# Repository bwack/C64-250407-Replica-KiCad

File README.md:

# The C64 250407 replica

A replica of the Commodore 64 Ver.250407  Rev.B motherboard, and matching schematics.

The replica project was started by Michael K. (Der Alte Bastler) in 2019 to learn SprintLayout, and the process of reverse engineering printed circuit boards. I finished the layout in SprintLayout, and imported it to KiCad. The KU motherboard schematics are nowhere to be found on the internet. Therefore I used the 250407 Reb.B schematics as reference and then modified them to match the KU motherboard layout.

The board has been prototyped and tested by Langwell Cowan and I.

We are not the first to reverse engineer this board; but we are the first to share the design files online.

# BOM

Please see the [BOM file](250407_bom.csv).

Note that some values were left blank because they depend on the clock circuit (PAL/NTSC), and PLA model. They never made it into the schematics. You can find them in a table to the right of the schematics for 250407.
http://www.zimmers.net/anonftp/pub/cbm/schematics/computers/c64/index.html

# Interactive-BOM

[The interactive bom html page](https://htmlpreview.github.io/?https://raw.githubusercontent.com/bwack/C64-250407-Replica-KiCad/main/interactive-bom/ibom.html) is a useful tool for assembling the board and finding signal traces via a web browser. To order parts, Use the BOM document listed above. (Mouser and Digikey compatable)

# Schematics

Download the PDF file [250407_.pdf](250407_.pdf) for high quality schematics.
Checkout [this tweet](https://twitter.com/paulrickards/status/1371988589974847492) by Paul Rickards where he plots the KU motherboard schematics KU-14194HB :-)

# Change log
- 2025-06-09: PCB and Schematics V1.3: PAL-NTSC jumpers fox. Thank you, Fred Sauer!
Note: V1.3 was opened and saved in KiCAD 9.0.1. I've verified the new gerbers. Things to beware of I you want to modify the design: 1. If you try to load changes from schematic into the PCBNew, KiCAD will require you to annotate the schematics, which in turn will replace all the resistor array sub parts. Example R1A will become R1A1, which will turn into new parts in PCBNew. Therefore I have not done that in this update. I have only changed the silkscreen, and I have only edited the schematics. 2. KiCAD will ask you to refill the zone fills. I have not done that because it also warns you about some change in fill-constrains. I don't remember exactly what, but I did not refill the fill zones when going to V1.3.
- 2022-08-18: Schematics V1.2: symbol and ERC fixes (Pull request from Gabriele Gorla/GGLABS)
- 2020-06-19: PCB and schematics V1.1: First release
- 2020-04-22: PCB and schematics V1.0: Prototype

# YouTube

Part 1-4:

# License and Disclaimer

Copyright Bwack 2025

This documentation describes Open Hardware and is licensed under the CERN OHL v. 1.2.

You may redistribute and modify this documentation under the terms of theCERN OHL v.1.2. (http://ohwr.org/cernohl). This documentation is distributed WITHOUT ANY EXPRESS OR IMPLIED WARRANTY, INCLUDING OF MERCHANTABILITY, SATISFACTORY QUALITY AND FITNESS FOR APARTICULAR PURPOSE. Please see the CERN OHL v.1.2 for applicable conditions.

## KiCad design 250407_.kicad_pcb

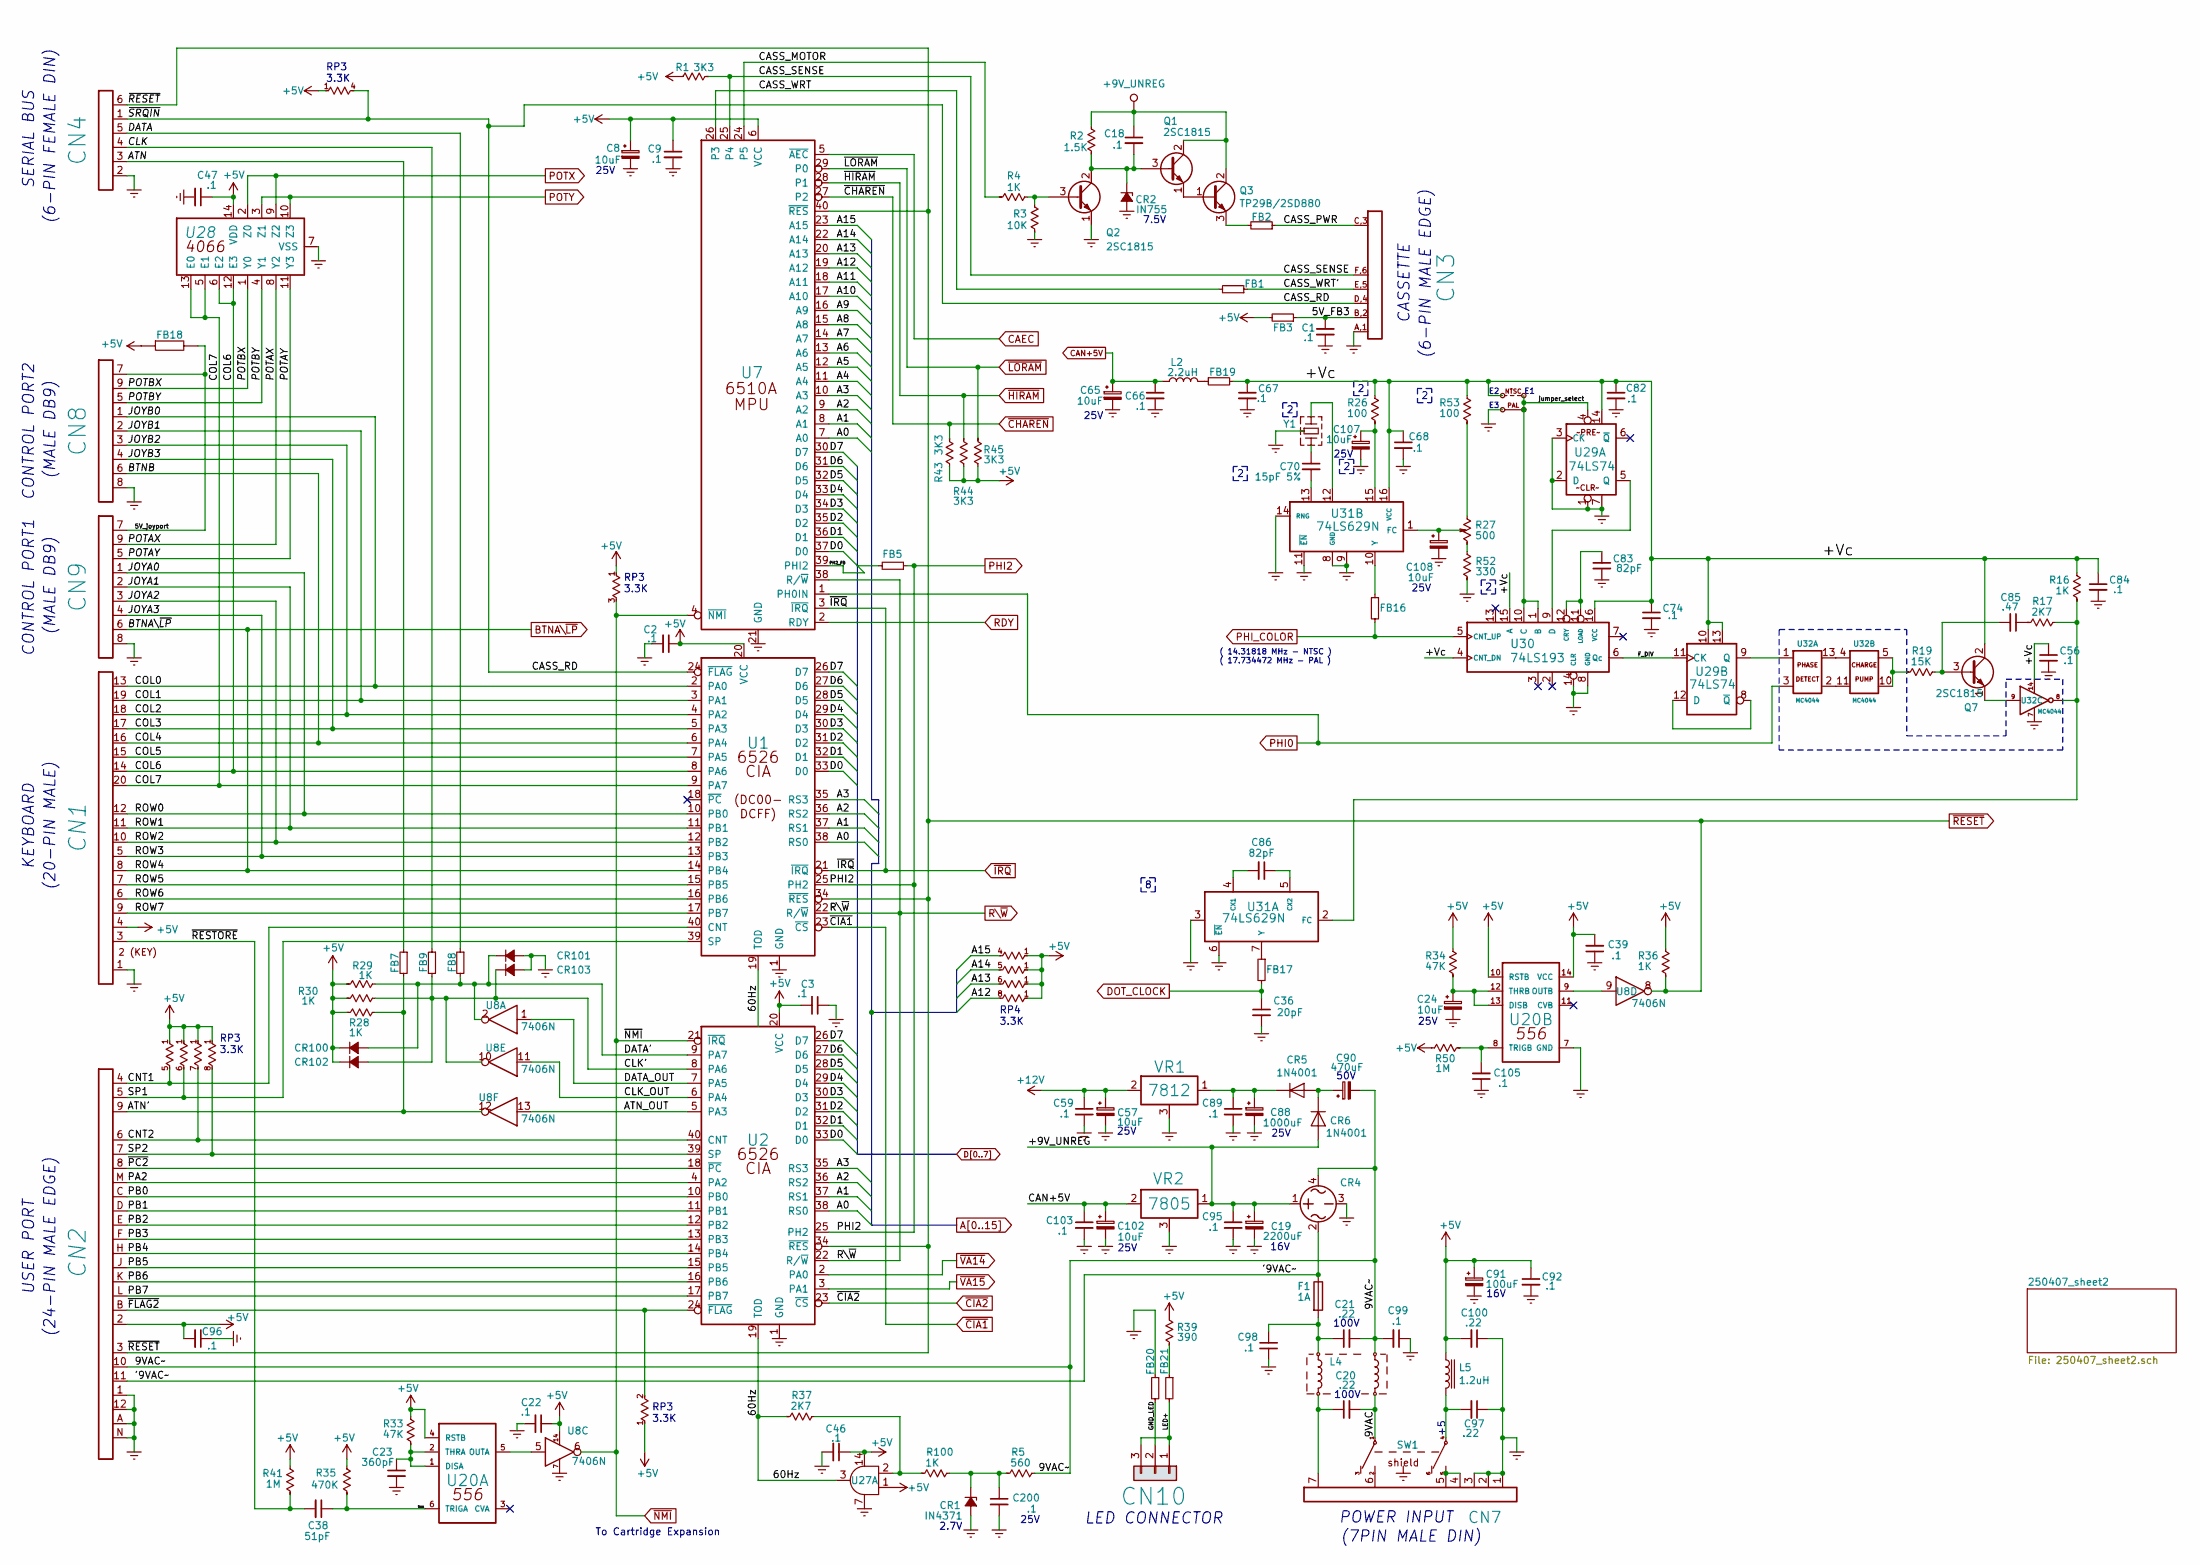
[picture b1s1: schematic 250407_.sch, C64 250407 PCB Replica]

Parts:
C1, C2, C3, C9, C18, C22, C39, C46, C47, C56, C59, C66, C67, C68, C74, C82, C84, C89, C92, C95, C96, C98, C99, C103, C105, C200: .1; CAP_P5.08mm
C8, C24, C57, C65, C102, C107, C108: 10uF; CAP_ELYT_RADIAL_P5.08mm_SMALL_RING
C19: 2200uF; LARGE_ELECTROLYTIC_AXIAL_TH
C20, C21: .22; CAP_POLY_100V_TH_P5.08_and_P12.07mm
C23: 360pF; CAP_AXIAL_P12.7mm
C36: 20pF; RESISTOR
C38: 51pF; CAP_AXIAL_P12.7mm
C70: 15pF 5%; RESISTOR
C83, C86: 82pF; RESISTOR
C85: .47; CAP_P5.08mm
C88: 1000uF; LARGE_ELECTROLYTIC_AXIAL_TH
C90: 470uF; LARGE_ELECTROLYTIC_AXIAL_TH
C91: 100uF; CAP_ELYT_RADIAL_P5.08mm
C97, C100: .22; CAP_P5.08mm
CN1: KEYBOARD_20PIN_MALE; KEYBOARD_CON
CN2: USER_PORT_CON; EDGE_CON_24P
CN3: CASSETTE_PORT_CON; EDGE_CON_12P_TAPE
CN4: SERIAL_BUS_CON; SERIAL_CON_DIN6
CN7: POWER_CON; POWER_CON_D7_250407
CN8, CN9: CONTROL_PORT; JOYPORT_DB9
CN10: LED_CONNECTOR; LED_CON
CR1: IN4371; ZENER_12.7mm
CR2: IN755; ZENER_12.7mm
CR4: BRIDGE_RECTIFIER
CR5, CR6: 1N4001; RECTIFIER_TH_P12.7mm
CR100, CR101, CR102, CR103: D_Small_ALT
E1: JUMPER_WIRE
E2: JUMPER_WIRE_DASHED; JUMPER_WIRE
F1: 1A; FUSE
FB1, FB2, FB3, FB5, FB7, FB8, FB9, FB16, FB17, FB18, FB19, FB20, FB21: FERRITE_BEAD; FERRITE_BEAD_TH_P12.7mm
L2: 2.2uH; RESISTOR
L4: CHOKE
L5: 1.2uH; INDUCTOR_P15.24mm
Q1, Q2, Q7: 2SC1815; Q_NPN_ECB
Q3: TP29B/2SD880; TO-220-3_Horizontal_TabDown_250407
R1, R43, R44, R45: 3K3; RESISTOR
R2: 1.5K; RESISTOR
R3: 10K; RESISTOR
R4, R16, R28, R29, R30, R36, R100: 1K; RESISTOR
R5: 560; RESISTOR
R17, R37: 2K7; RESISTOR
R19: 15K; RESISTOR
R26, R53: 100; RESISTOR
R27: 500; POTMETER
R33, R34: 47K; RESISTOR
R35: 470K; RESISTOR
R39: 390; RESISTOR
R41, R50: 1M; RESISTOR
R52: 330; RESISTOR
RP3: 3K3 Bussed; RP_ARRAY_7WAY
RP4: 3K3 Bussed; RP_ARRAY_9WAY
SW1: POWER_SWITCH
U1: CIA_U1; DIP40
U2: CIA_U2; DIP40
U7: 6510_MPU; DIP40
U8: 7406N; DIP14
U20: 556; DIP14
U27: 7408_U27; DIP14
U28: 4066_U28; DIP14
U29: 74LS74; DIP14
U30: 74LS193; DIP16
U31: 74LS629N; DIP16
U32: MC4044; DIP14
VR1: 7812; VREG_TO-220-3_Horizontal_TabDown
VR2: 7805; VREG_TO-220-3_Horizontal_TabDown
Y1: Crystal; CRYSTAL

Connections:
+5V: C2.1, C3.2, C8.1, C9.1, C22.1, C39.2, C46.1, C47.1, C91.1, C92.1, C96.2, C100.2, CN1.4, CN2.2, CR100.1 (K), CR102.1 (K), FB3.2, FB18.1, L5.1, R1.1, R28.2, R29.2, R30.2, R33.1, R34.1, R35.1, R36.1, R39.1, R41.1, R43.1, R44.1, R45.1, R50.1, RP3.1, RP4.1, U1.20 (VCC), U2.20 (VCC), U7.6 (VCC), U8.14, U20.4 (RSTB), U20.10 (RSTB), U20.14 (VCC), U27.1, U27.14, U28.14 (VDD); also elsewhere on the board
+9V_UNREG: C18.1, C19.1, C95.1, CR4.1, CR6.2 (A), Q1.2 (C), Q3.2 (C), R2.1, VR2.1; also elsewhere on the board
+12V: C57.1, C59.1, VR1.2; also elsewhere on the board
/5V_FB3: C1.1, CN3.B,2, FB3.1
/5V_joyport: CN8.7, CN9.7, FB18.2
/9VAC: C20.2, L4.3, SW1.1
/9VAC~~: C21.2, C90.2, C99.2, CN2.10, CR4.4, L4.4, R5.1
/60Hz: R37.2, U1.19 (TOD), U2.19 (TOD), U27.3
/'9VAC~~: CN2.11, CR4.2, F1.1
/+Vc: C56.1, C67.1, C68.1, C74.1, C82.1, C84.1, E2.1, FB19.2, Q7.2 (C), R16.1, R26.1, R53.1, U29.10, U29.13, U29.14, U30.4 (CNT_DN), U30.15 (A), U30.16 (VCC), U31.16 (VCC), U32.14
/ATN: CN4.3, FB7.1
/ATN': CN2.9, FB7.2, R28.1, U8.12
/ATN_OUT: U2.5 (PA3), U8.13
/BTNB: CN1.16, CN8.6, U1.6 (PA4)
/CASS_MOTOR: R4.2, U7.24 (P5)
/CASS_PWR: CN3.C,3, FB2.1
/CASS_RD: CN3.D,4, CN4.1, RP3.4, U1.24 (~FLAG~)
/CASS_SENSE: CN3.F,6, R1.2, U7.25 (P4)
/CASS_WRT: FB1.2, U7.26 (P3)
/CASS_WRT': CN3.E,5, FB1.1
/CLK: CN4.4, FB9.1
/CLK': CR102.2 (A), CR103.1 (K), FB9.2, R30.1, U2.8 (PA6), U8.10
/CLK_OUT: U2.6 (PA4), U8.11
/CNT1: CN2.4, RP3.5, U1.40 (CNT)
/CNT2: CN2.6, RP3.7, U2.40 (CNT)
/COL0: CN1.13, CN8.1, U1.2 (PA0)
/COL1: CN1.19, CN8.2, U1.3 (PA1)
/COL2: CN1.18, CN8.3, U1.4 (PA2)
/COL3: CN1.17, CN8.4, U1.5 (PA3)
/COL5: CN1.15, U1.7 (PA5)
/COL6: CN1.14, U1.8 (PA6), U28.6 (E2), U28.12 (E3)
/COL7: CN1.20, U1.9 (PA7), U28.5 (E1), U28.13 (E0)
/DATA: CN4.5, FB8.1
/DATA': CR100.2 (A), CR101.1 (K), FB8.2, R29.1, U2.9 (PA7), U8.2
/DATA_OUT: U2.7 (PA5), U8.1
/F_DIV: U29.11 (CK), U30.6 (Qc)
/GND_LED: CN10.2, FB20.2
/JOYA0: CN1.12, CN9.1, U1.10 (PB0)
/JOYA1: CN1.11, CN9.2, U1.11 (PB1)
/JOYA2: CN1.10, CN9.3, U1.12 (PB2)
/JOYA3: CN1.5, CN9.4, U1.13 (PB3)
/LED+: CN10.1, CN10.3, FB21.2
/PA2: CN2.M, U2.4 (PA2)
/PB0: CN2.C, U2.10 (PB0)
/PB1: CN2.D, U2.11 (PB1)
/PB2: CN2.E, U2.12 (PB2)
/PB3: CN2.F, U2.13 (PB3)
/PB4: CN2.H, U2.14 (PB4)
/PB5: CN2.J, U2.15 (PB5)
/PB6: CN2.K, U2.16 (PB6)
/PB7: CN2.L, U2.17 (PB7)
/PH2_FB: FB5.2, U7.39 (PHI2)
/POTAX: CN9.9, U28.8 (Y2)
/POTAY: CN9.5, U28.11 (Y3)
/POTBX: CN8.9, U28.1 (Y0)
/POTBY: CN8.5, U28.4 (Y1)
/ROW5: CN1.7, U1.15 (PB5)
/ROW6: CN1.6, U1.16 (PB6)
/ROW7: CN1.9, U1.17 (PB7)
/SP1: CN2.5, RP3.6, U1.39 (SP)
/SP2: CN2.7, RP3.8, U2.39 (SP)
/TRIGA: C38.1, R35.2, U20.6 (TRIGA)
/jumper_select: E1.2, E2.2, U29.4, U30.1 (B), U30.10 (C)
/~FLAG2~: CN2.B, RP3.2, U2.24 (~FLAG~)
/~PC2~: CN2.8, U2.18 (~PC~)
/~RESTORE~: C38.2, CN1.3, R41.2
A0: U1.38 (RS0), U2.38 (RS0), U7.7 (A0); also elsewhere on the board
A1: U1.37 (RS1), U2.37 (RS1), U7.8 (A1); also elsewhere on the board
A2: U1.36 (RS2), U2.36 (RS2), U7.9 (A2); also elsewhere on the board
A3: U1.35 (RS3), U2.35 (RS3), U7.10 (A3); also elsewhere on the board
A4: U7.11 (A4); also elsewhere on the board
A5: U7.12 (A5); also elsewhere on the board
A6: U7.13 (A6); also elsewhere on the board
A7: U7.14 (A7); also elsewhere on the board
A8: U7.15 (A8); also elsewhere on the board
A9: U7.16 (A9); also elsewhere on the board
A10: U7.17 (A10); also elsewhere on the board
A11: U7.18 (A11); also elsewhere on the board
A12: RP4.8, U7.19 (A12); also elsewhere on the board
A13: RP4.6, U7.20 (A13); also elsewhere on the board
A14: RP4.5, U7.22 (A14); also elsewhere on the board
A15: RP4.4, U7.23 (A15); also elsewhere on the board
BTNA\~LP~: CN1.8, CN9.6, U1.14 (PB4); also elsewhere on the board
CAEC: U7.5 (~AEC~); also elsewhere on the board
CAN+5V: C65.1, C66.1, C102.1, C103.1, L2.1, VR2.2; also elsewhere on the board
D0: U1.33 (D0), U2.33 (D0), U7.37 (D0); also elsewhere on the board
D1: U1.32 (D1), U2.32 (D1), U7.36 (D1); also elsewhere on the board
D2: U1.31 (D2), U2.31 (D2), U7.35 (D2); also elsewhere on the board
D3: U1.30 (D3), U2.30 (D3), U7.34 (D3); also elsewhere on the board
D4: U1.29 (D4), U2.29 (D4), U7.33 (D4); also elsewhere on the board
D5: U1.28 (D5), U2.28 (D5), U7.32 (D5); also elsewhere on the board
D6: U1.27 (D6), U2.27 (D6), U7.31 (D6); also elsewhere on the board
D7: U1.26 (D7), U2.26 (D7), U7.30 (D7); also elsewhere on the board
DOT_CLOCK: C36.1, FB17.2; also elsewhere on the board
Earth: C1.2, C2.2, C3.1, C8.2, C9.2, C19.2, C22.2, C23.2, C24.2, C36.2, C39.1, C46.2, C47.2, C56.2, C57.2, C59.2, C65.2, C66.2, C67.2, C68.2, C74.2, C82.2, C83.2, C84.2, C88.2, C89.2, C91.2, C92.2, C95.2, C96.1, C97.1, C98.2, C99.1, C100.1, C102.2, C103.2, C105.1, C107.2, C108.2, C200.2, CN1.1, CN2.1, CN2.12, CN2.A, CN2.N, CN3.A,1, CN4.2, CN7.1, CN7.2, CN7.3, CN8.8, CN9.8, CR1.2 (A), CR2.2 (A), CR4.3, CR101.2 (A), CR103.2 (A), E1.1, FB20.1, Q2.1 (E), R3.2, R52.2, SW1.~ (pe), U1.1 (GND), U2.1 (GND), U7.21 (GND), U8.7, U20.7 (GND), U27.7, U28.7 (VSS), U29.1, U29.2 (D), U29.3 (CK), U29.7, U30.8 (GND), U30.14 (CLR), U31.3, U31.6 (~EN~), U31.8 (GND), U31.9, U31.11 (~EN~), U31.14 (RNG), U32.7, VR1.3, VR2.3, Y1.3; also elsewhere on the board
unnamed: C18.2, CR2.1 (K), Q1.3 (B), Q2.2 (C), R2.2
unnamed: C20.1, CN7.7, L4.2
unnamed: C21.1, C98.1, F1.2, L4.1
unnamed: C23.1, R33.2, U20.1 (DISA), U20.2 (THRA)
unnamed: C24.1, R34.2, U20.12 (THRB), U20.13 (DISB)
unnamed: C70.1, Y1.2
unnamed: C70.2, U31.13
unnamed: C83.1, U30.11 (LOAD), U30.12 (CRY)
unnamed: C85.1, R17.2
unnamed: C85.2, Q7.3 (B), R19.1
unnamed: C86.1, U31.5 (CX2)
unnamed: C86.2, U31.4 (CX1)
unnamed: C88.1, C89.1, CR5.1 (K), VR1.1
unnamed: C90.1, CR5.2 (A), CR6.1 (K)
unnamed: C97.2, L5.2, SW1.4
unnamed: C105.2, R50.2, U20.8 (TRIGB)
unnamed: C107.1, R26.2, U31.15
unnamed: C108.1, R27.3, U31.1 (FC)
unnamed: C200.1, CR1.1 (K), R5.2, R100.1
unnamed: CN7.4, CN7.5, SW1.5
unnamed: CN7.6, SW1.2
unnamed: FB2.2, Q3.3 (E)
unnamed: FB16.1, U31.10 (Y)
unnamed: FB17.1, U31.7 (Y)
unnamed: FB19.1, L2.2
unnamed: FB21.1, R39.2
unnamed: Q1.1 (E), Q3.1 (B)
unnamed: Q2.3 (B), R3.1, R4.1
unnamed: Q7.1 (E), U32.9
unnamed: R16.2, R17.1, U31.2 (FC), U32.8
unnamed: R19.2, U32.5, U32.10
unnamed: R27.1, R53.2
unnamed: R27.2, R52.1
unnamed: R37.1, R100.2, U27.2
unnamed: U8.5, U20.5 (OUTA)
unnamed: U8.9, U20.9 (OUTB)
unnamed: U29.5 (Q), U30.9 (D)
unnamed: U29.9 (Q), U32.1
unnamed: U29.8 (~Q~), U29.12 (D)
unnamed: U31.12, Y1.1
unnamed: U32.2, U32.11
unnamed: U32.4, U32.13
PHI0: U7.1 (PH0IN), U32.3; also elsewhere on the board
PHI2: FB5.1, U1.25 (PH2), U2.25 (PH2); also elsewhere on the board
PHI_COLOR: FB16.2, U30.5 (CNT_UP); also elsewhere on the board
POTX: U28.2 (Z0), U28.9 (Z2); also elsewhere on the board
POTY: U28.3 (Z1), U28.10 (Z3); also elsewhere on the board
RDY: U7.2 (RDY); also elsewhere on the board
R\~W~: U1.22 (R/~W~), U2.22 (R/~W~), U7.38 (R/~W~); also elsewhere on the board
~CHAREN~: R43.2, U7.27 (P2); also elsewhere on the board
~CIA1~: U1.23 (~CS~); also elsewhere on the board
~CIA2~: U2.23 (~CS~); also elsewhere on the board
~HIRAM~: R44.2, U7.28 (P1); also elsewhere on the board
~IRQ~: U1.21 (~IRQ~), U7.3 (~IRQ~); also elsewhere on the board
~LORAM~: R45.2, U7.29 (P0); also elsewhere on the board
~NMI~: RP3.3, U2.21 (~IRQ~), U7.4 (~NMI~), U8.6; also elsewhere on the board
~RESET~: CN2.3, CN4.6, R36.2, U1.34 (~RES~), U2.34 (~RES~), U7.40 (~RES~), U8.8; also elsewhere on the board
~VA14~: U2.2 (PA0); also elsewhere on the board
~VA15~: U2.3 (PA1); also elsewhere on the board

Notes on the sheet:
SERIAL BUS
(6-PIN FEMALE DIN)
(24-PIN MALE EDGE)
USER PORT
RP3 3.3K
KEYBOARD
(20-PIN MALE)
(MALE DB9)
CONTROL PORT2
CONTROL PORT1
25V
2.7V
RP4 3.3K
7.5V
(6-PIN MALE EDGE)
CASSETTE
LED CONNECTOR
100V
POWER INPUT
(7PIN MALE DIN)
16V
50V
( 14.31818 MHz - NTSC ) ( 17.734472 MHz - PAL )
To Cartridge Expansion

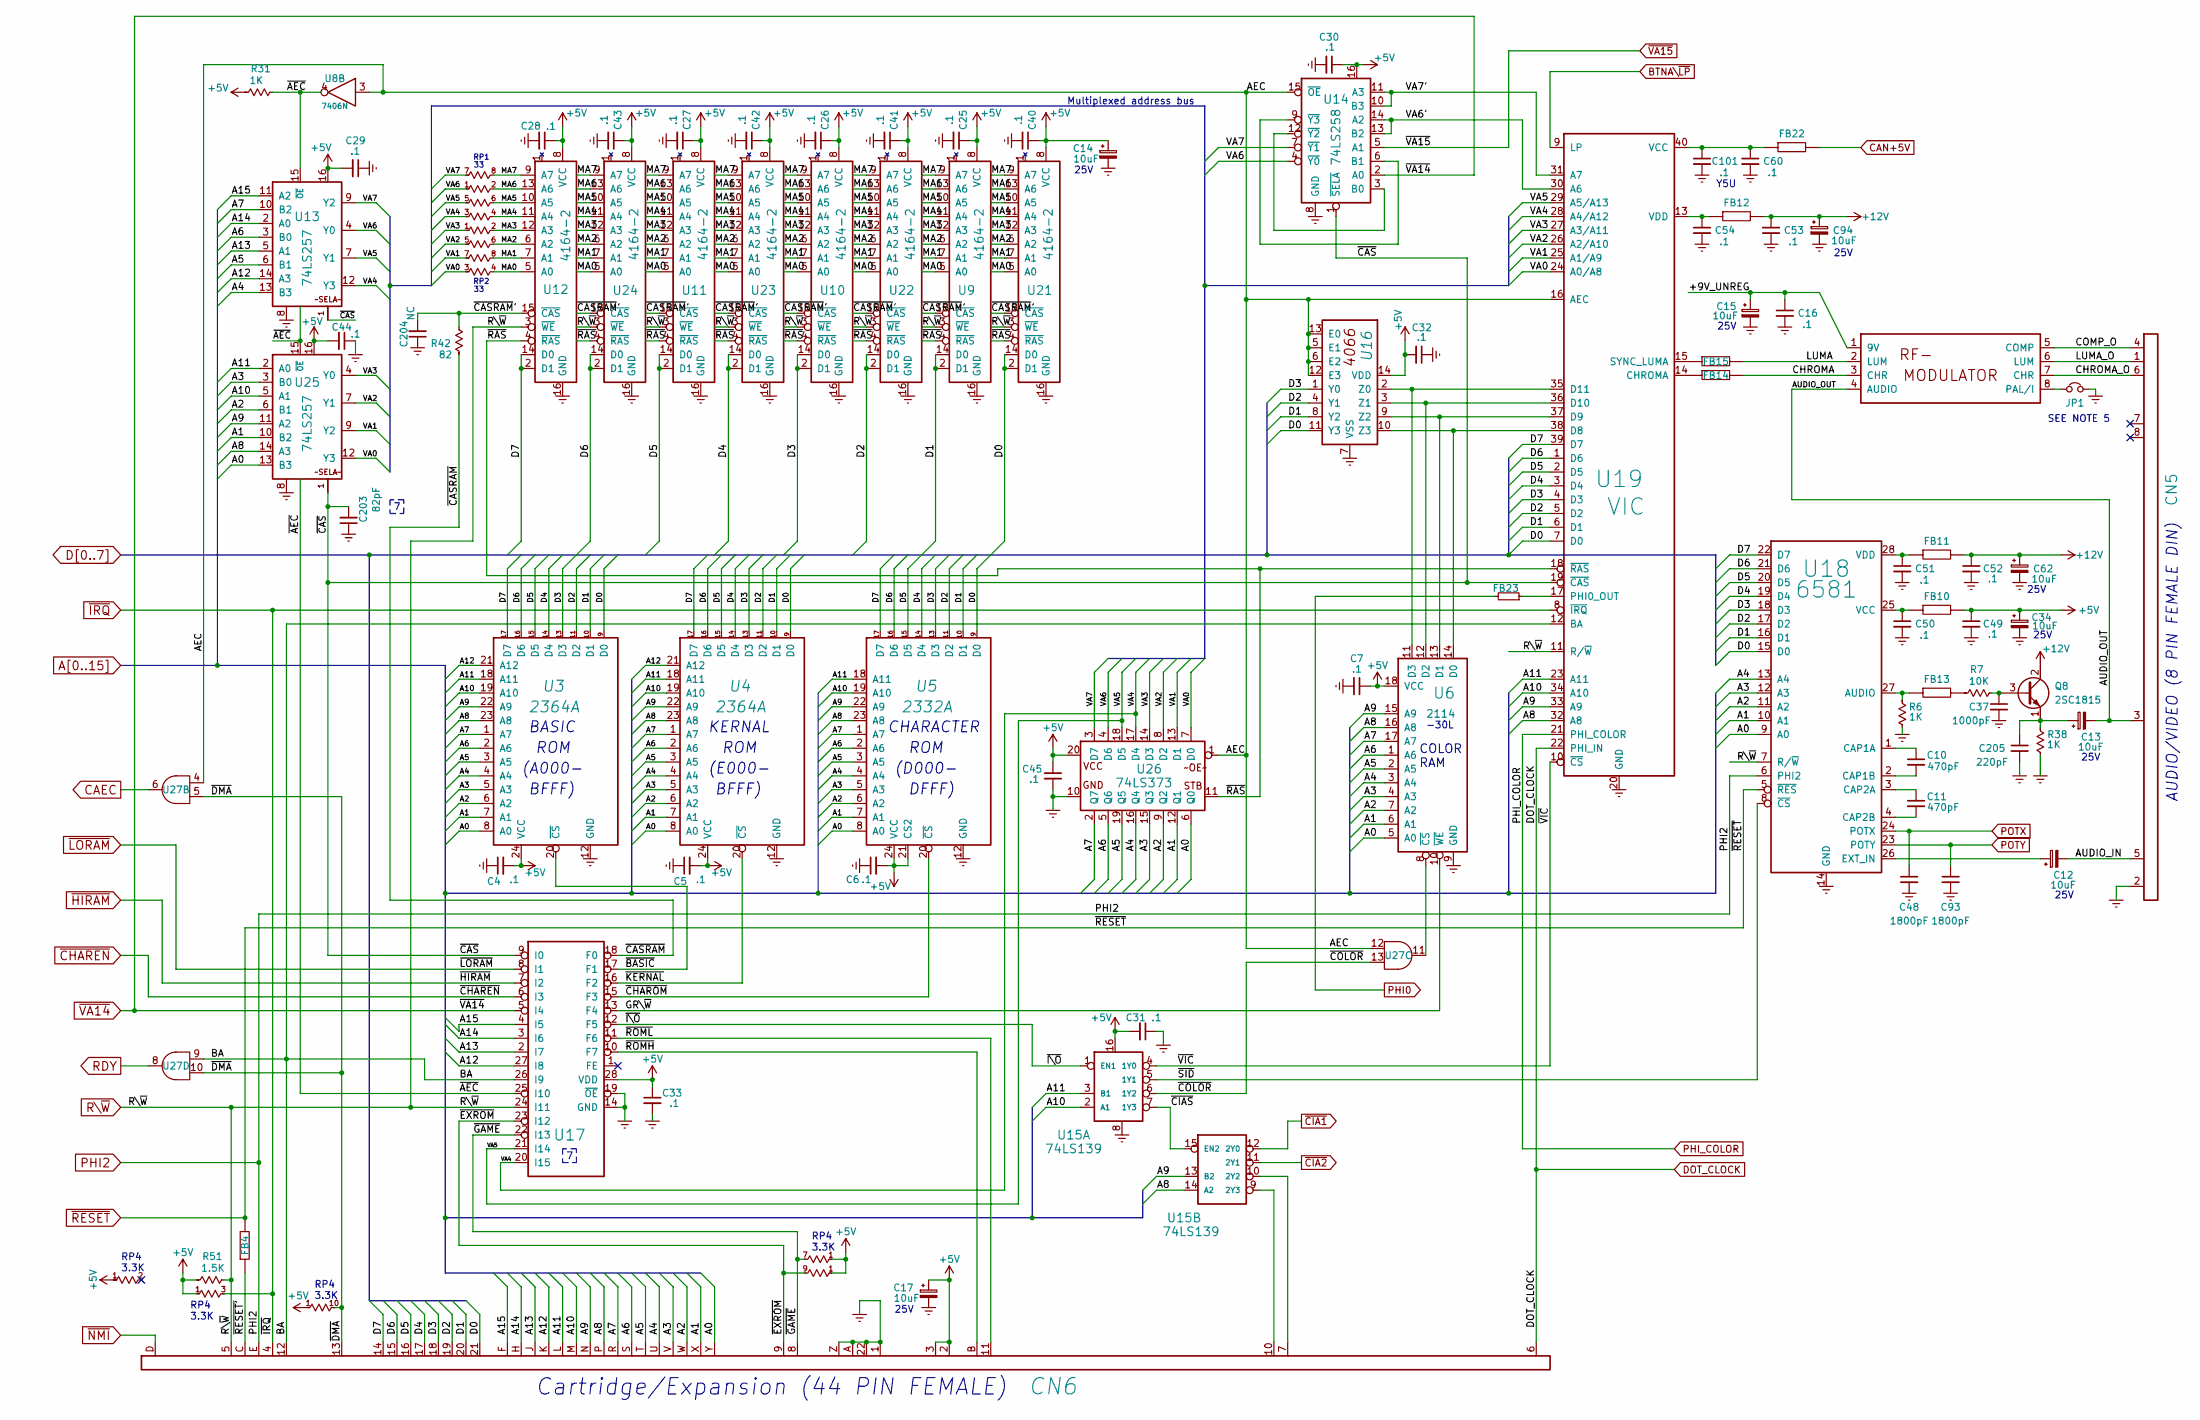
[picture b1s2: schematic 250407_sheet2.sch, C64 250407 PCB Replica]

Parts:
C4, C5, C6, C7, C16, C25, C26, C27, C28, C29, C30, C31, C32, C33, C40, C41, C42, C43, C44, C45, C49, C50, C51, C52, C53, C54, C60, C101: .1; CAP_P5.08mm
C10, C11: 470pF; CAP_P5.08mm
C12, C13, C14, C15, C17, C34, C62, C94: 10uF; CAP_ELYT_RADIAL_P5.08mm_SMALL_RING
C37: 1000pF; CAP_P5.08mm
C48, C93: 1800pF; CAP_P5.08mm
C203: 82pF; CAPACITOR_RADIAL_P13.97_L9.9_D3.6
C204: NC; CAP_P5.08mm
C205: 220pF; CAP_P5.08mm
CN5: AV_CONN; AV_CON_DIN8
CN6: EXPANSION_PORT
FB4, FB10, FB11, FB12, FB13, FB14, FB15, FB22, FB23: FERRITE_BEAD; FERRITE_BEAD_TH_P12.7mm
JP1: Jumper_NC_Small; SolderJumper-2_P1.3mm_Bridged_RoundedPad1.0x1.5mm
M1: MODULATOR_LONGBOARD; MODULATOR_PORT_LONGBOARD
Q8: 2SC1815; Q_NPN_ECB
R6, R31, R38: 1K; RESISTOR
R7: 10K; RESISTOR
R42: 82; RESISTOR
R51: 1.5K; RESISTOR
RP1, RP2: 33R isolated; RP_ARRAY_7WAY
RP4: 3K3 Bussed; RP_ARRAY_9WAY
U3, U4: 2364A; DIP24
U5: 2332A; DIP24
U6: 2114; DIP18
U8: 7406N; DIP14
U9, U10, U11, U12, U21, U22, U23, U24: 4164-2; DIP16
U13, U25: 74LS257; DIP16
U14: 74LS258; DIP16
U15: 74LS139; DIP16
U16: 4066_U28; DIP14
U17: PLA_U17; DIP28
U18: 6581; DIP28
U19: VIC; DIP40
U26: 74LS373; DIP20
U27: 7408_U27; DIP14

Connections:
+5V: C4.2, C5.2, C6.2, C7.1, C14.1, C17.1, C25.1, C26.1, C27.1, C28.1, C29.2, C30.1, C31.2, C32.2, C33.1, C34.1, C40.1, C41.1, C42.1, C43.1, C44.2, C45.1, C49.1, CN6.2, CN6.3, FB10.2, R31.2, R51.2, RP4.1, U3.24 (VCC), U4.24 (VCC), U5.21 (CS2), U5.24 (VCC), U6.18 (VCC), U9.8 (VCC), U10.8 (VCC), U11.8 (VCC), U12.8 (VCC), U13.16, U14.16, U15.16, U16.14 (VDD), U17.28 (VDD), U21.8 (VCC), U22.8 (VCC), U23.8 (VCC), U24.8 (VCC), U25.16, U26.20; also elsewhere on the board
+9V_UNREG: C15.1, C16.1, M1.1 (9V); also elsewhere on the board
+12V: C52.1, C53.1, C62.1, C94.1, FB11.2, FB12.2, Q8.2 (C); also elsewhere on the board
/250407_sheet2/AEC: U8.3, U14.15 (~OE~), U16.5 (E1), U16.6 (E2), U16.12 (E3), U16.13 (E0), U19.16 (AEC), U26.1, U27.4, U27.12
/250407_sheet2/AUDIO_IN: C12.2, CN5.5
/250407_sheet2/AUDIO_OUT: C13.2, CN5.3, M1.4 (AUDIO)
/250407_sheet2/BA: CN6.12, U17.26 (I9), U19.12 (BA), U27.9
/250407_sheet2/CHROMA: FB14.2, M1.3 (CHR)
/250407_sheet2/CHROMA_O: CN5.6, M1.7 (CHR)
/250407_sheet2/COMP_O: CN5.4, M1.5 (COMP)
/250407_sheet2/GR\~W~: U6.10 (~WE~), U17.13 (F4)
/250407_sheet2/LUMA: FB15.2, M1.2 (LUM)
/250407_sheet2/LUMA_O: CN5.1, M1.6 (LUM)
/250407_sheet2/MA0: RP2.4, U9.5 (A0), U10.5 (A0), U11.5 (A0), U12.5 (A0), U21.5 (A0), U22.5 (A0), U23.5 (A0), U24.5 (A0)
/250407_sheet2/MA1: RP2.8, U9.7 (A1), U10.7 (A1), U11.7 (A1), U12.7 (A1), U21.7 (A1), U22.7 (A1), U23.7 (A1), U24.7 (A1)
/250407_sheet2/MA2: RP2.6, U9.6 (A2), U10.6 (A2), U11.6 (A2), U12.6 (A2), U21.6 (A2), U22.6 (A2), U23.6 (A2), U24.6 (A2)
/250407_sheet2/MA3: RP2.2, U9.12 (A3), U10.12 (A3), U11.12 (A3), U12.12 (A3), U21.12 (A3), U22.12 (A3), U23.12 (A3), U24.12 (A3)
/250407_sheet2/MA4: RP1.4, U9.11 (A4), U10.11 (A4), U11.11 (A4), U12.11 (A4), U21.11 (A4), U22.11 (A4), U23.11 (A4), U24.11 (A4)
/250407_sheet2/MA5: RP1.6, U9.10 (A5), U10.10 (A5), U11.10 (A5), U12.10 (A5), U21.10 (A5), U22.10 (A5), U23.10 (A5), U24.10 (A5)
/250407_sheet2/MA6: RP1.2, U9.13 (A6), U10.13 (A6), U11.13 (A6), U12.13 (A6), U21.13 (A6), U22.13 (A6), U23.13 (A6), U24.13 (A6)
/250407_sheet2/MA7: RP1.8, U9.9 (A7), U10.9 (A7), U11.9 (A7), U12.9 (A7), U21.9 (A7), U22.9 (A7), U23.9 (A7), U24.9 (A7)
/250407_sheet2/VA0: RP2.3, U19.24 (A0/A8), U25.12 (Y3), U26.7 (D0)
/250407_sheet2/VA1: RP2.7, U19.25 (A1/A9), U25.9 (Y2), U26.13 (D1)
/250407_sheet2/VA2: RP2.5, U19.26 (A2/A10), U25.7 (Y1), U26.8 (D2)
/250407_sheet2/VA3: RP2.1, U19.27 (A3/A11), U25.4 (Y0), U26.14 (D3)
/250407_sheet2/VA4: RP1.3, U13.12 (Y3), U17.20 (I15), U19.28 (A4/A12), U26.17 (D4)
/250407_sheet2/VA5: RP1.5, U13.7 (Y1), U17.21 (I14), U19.29 (A5/A13), U26.18 (D5)
/250407_sheet2/VA6: RP1.1, U13.4 (Y0), U14.4 (~Y0~), U26.4 (D6)
/250407_sheet2/VA6': U14.13 (B2), U14.14 (A2), U19.30 (A6)
/250407_sheet2/VA7: RP1.7, U13.9 (Y2), U14.7 (~Y1~), U26.3 (D7)
/250407_sheet2/VA7': U14.10 (B3), U14.11 (A3), U19.31 (A7)
/250407_sheet2/~AEC~: R31.1, U8.4, U13.15 (~OE~), U17.25 (I10), U25.15 (~OE~)
/250407_sheet2/~BASIC~: U3.20 (~CS~), U17.17 (F1)
/250407_sheet2/~CASRAM~: R42.2, U17.18 (F0)
/250407_sheet2/~CASRAM~': C204.2, R42.1, U9.15 (~CAS~), U10.15 (~CAS~), U11.15 (~CAS~), U12.15 (~CAS~), U21.15 (~CAS~), U22.15 (~CAS~), U23.15 (~CAS~), U24.15 (~CAS~)
/250407_sheet2/~CAS~: C203.2, U13.1 (~SELA~), U14.1 (~SELA~), U17.9 (I0), U19.19 (~CAS~), U25.1 (~SELA~)
/250407_sheet2/~CHAROM~: U5.20 (~CS~), U17.15 (F3)
/250407_sheet2/~CIAS~: U15.7 (1Y3), U15.15 (EN2)
/250407_sheet2/~COLOR~: U15.6 (1Y2), U27.13
/250407_sheet2/~DMA~: CN6.13, RP4.10, U27.5, U27.10
/250407_sheet2/~EXROM~: CN6.9, RP4.9, U17.23 (I12)
/250407_sheet2/~GAME~: CN6.8, RP4.7, U17.22 (I13)
/250407_sheet2/~I\O~: U15.1 (EN1), U17.12 (F5)
/250407_sheet2/~KERNAL: U4.20 (~CS~), U17.16 (F2)
/250407_sheet2/~RAS~: U9.4 (~RAS~), U10.4 (~RAS~), U11.4 (~RAS~), U12.4 (~RAS~), U19.18 (~RAS~), U21.4 (~RAS~), U22.4 (~RAS~), U23.4 (~RAS~), U24.4 (~RAS~), U26.11
/250407_sheet2/~RESET'~: CN6.C, FB4.1
/250407_sheet2/~ROMH~: CN6.B, U17.10 (F7)
/250407_sheet2/~ROML~: CN6.11, U17.11 (F6)
/250407_sheet2/~SID~: U15.5 (1Y1), U18.8 (~CS~)
/250407_sheet2/~VIC~: U15.4 (1Y0), U19.10 (~CS~)
A0: CN6.Y, U3.8 (A0), U4.8 (A0), U5.8 (A0), U6.5 (A0), U18.9 (A0), U25.13 (B3), U26.6 (Q0); also elsewhere on the board
A1: CN6.X, U3.7 (A1), U4.7 (A1), U5.7 (A1), U6.6 (A1), U18.10 (A1), U25.10 (B2), U26.12 (Q1); also elsewhere on the board
A2: CN6.W, U3.6 (A2), U4.6 (A2), U5.6 (A2), U6.7 (A2), U18.11 (A2), U25.6 (B1), U26.9 (Q2); also elsewhere on the board
A3: CN6.V, U3.5 (A3), U4.5 (A3), U5.5 (A3), U6.4 (A3), U18.12 (A3), U25.3 (B0), U26.15 (Q3); also elsewhere on the board
A4: CN6.U, U3.4 (A4), U4.4 (A4), U5.4 (A4), U6.3 (A4), U13.13 (B3), U18.13 (A4), U26.16 (Q4); also elsewhere on the board
A5: CN6.T, U3.3 (A5), U4.3 (A5), U5.3 (A5), U6.2 (A5), U13.6 (B1), U26.19 (Q5); also elsewhere on the board
A6: CN6.S, U3.2 (A6), U4.2 (A6), U5.2 (A6), U6.1 (A6), U13.3 (B0), U26.5 (Q6); also elsewhere on the board
A7: CN6.R, U3.1 (A7), U4.1 (A7), U5.1 (A7), U6.17 (A7), U13.10 (B2), U26.2 (Q7); also elsewhere on the board
A8: CN6.P, U3.23 (A8), U4.23 (A8), U5.23 (A8), U6.16 (A8), U15.14 (A2), U19.32 (A8), U25.14 (A3); also elsewhere on the board
A9: CN6.N, U3.22 (A9), U4.22 (A9), U5.22 (A9), U6.15 (A9), U15.13 (B2), U19.33 (A9), U25.11 (A2); also elsewhere on the board
A10: CN6.M, U3.19 (A10), U4.19 (A10), U5.19 (A10), U15.2 (A1), U19.34 (A10), U25.5 (A1); also elsewhere on the board
A11: CN6.L, U3.18 (A11), U4.18 (A11), U5.18 (A11), U15.3 (B1), U19.23 (A11), U25.2 (A0); also elsewhere on the board
A12: CN6.K, U3.21 (A12), U4.21 (A12), U13.14 (A3), U17.27 (I8); also elsewhere on the board
A13: CN6.J, U13.5 (A1), U17.2 (I7); also elsewhere on the board
A14: CN6.H, U13.2 (A0), U17.3 (I6); also elsewhere on the board
A15: CN6.F, U13.11 (A2), U17.4 (I5); also elsewhere on the board
BTNA\~LP~: U19.9 (LP); also elsewhere on the board
CAEC: U27.6; also elsewhere on the board
CAN+5V: FB22.2; also elsewhere on the board
D0: CN6.21, U3.9 (D0), U4.9 (D0), U5.9 (D0), U16.11 (Y3), U18.15 (D0), U19.7 (D0), U21.2 (D1), U21.14 (D0); also elsewhere on the board
D1: CN6.20, U3.10 (D1), U4.10 (D1), U5.10 (D1), U9.2 (D1), U9.14 (D0), U16.8 (Y2), U18.16 (D1), U19.6 (D1); also elsewhere on the board
D2: CN6.19, U3.11 (D2), U4.11 (D2), U5.11 (D2), U16.4 (Y1), U18.17 (D2), U19.5 (D2), U22.2 (D1), U22.14 (D0); also elsewhere on the board
D3: CN6.18, U3.13 (D3), U4.13 (D3), U5.13 (D3), U10.2 (D1), U10.14 (D0), U16.1 (Y0), U18.18 (D3), U19.4 (D3); also elsewhere on the board
D4: CN6.17, U3.14 (D4), U4.14 (D4), U5.14 (D4), U18.19 (D4), U19.3 (D4), U23.2 (D1), U23.14 (D0); also elsewhere on the board
D5: CN6.16, U3.15 (D5), U4.15 (D5), U5.15 (D5), U11.2 (D1), U11.14 (D0), U18.20 (D5), U19.2 (D5); also elsewhere on the board
D6: CN6.15, U3.16 (D6), U4.16 (D6), U5.16 (D6), U18.21 (D6), U19.1 (D6), U24.2 (D1), U24.14 (D0); also elsewhere on the board
D7: CN6.14, U3.17 (D7), U4.17 (D7), U5.17 (D7), U12.2 (D1), U12.14 (D0), U18.22 (D7), U19.39 (D7); also elsewhere on the board
DOT_CLOCK: CN6.6, U19.22 (PHI_IN); also elsewhere on the board
Earth: C4.1, C5.1, C6.1, C7.2, C14.2, C15.2, C16.2, C17.2, C25.2, C26.2, C27.2, C28.2, C29.1, C30.2, C31.1, C32.1, C33.2, C34.2, C37.2, C40.2, C41.2, C42.2, C43.2, C44.1, C45.2, C48.2, C49.2, C50.2, C51.2, C52.2, C53.2, C54.2, C60.2, C62.2, C93.2, C94.2, C101.2, C203.1, C204.1, C205.2, CN5.2, CN6.1, CN6.22, CN6.A, CN6.Z, JP1.2, R6.1, R38.1, U3.12 (GND), U4.12 (GND), U5.12 (GND), U6.9 (GND), U9.16 (GND), U10.16 (GND), U11.16 (GND), U12.16 (GND), U13.8, U14.8 (GND), U15.8, U16.7 (VSS), U17.14 (GND), U17.19 (~OE~), U18.14 (GND), U19.20 (GND), U21.16 (GND), U22.16 (GND), U23.16 (GND), U24.16 (GND), U25.8, U26.10; also elsewhere on the board
unnamed: C10.1, U18.1 (CAP1A)
unnamed: C10.2, U18.2 (CAP1B)
unnamed: C11.1, U18.3 (CAP2A)
unnamed: C11.2, U18.4 (CAP2B)
unnamed: C12.1, U18.26 (EXT_IN)
unnamed: C13.1, C205.1, Q8.1 (E), R38.2
unnamed: C37.1, Q8.3 (B), R7.1
unnamed: C50.1, FB10.1, U18.25 (VCC)
unnamed: C51.1, FB11.1, U18.28 (VDD)
unnamed: C54.1, FB12.1, U19.13 (VDD)
unnamed: C60.1, C101.1, FB22.1, U19.40 (VCC)
unnamed: CN6.7, U15.10 (2Y2)
unnamed: CN6.10, U15.9 (2Y3)
unnamed: FB13.1, R6.2, U18.27 (AUDIO)
unnamed: FB13.2, R7.2
unnamed: FB14.1, U19.14 (CHROMA)
unnamed: FB15.1, U19.15 (SYNC_LUMA)
unnamed: FB23.1, U19.17 (PHI0_OUT)
unnamed: JP1.1, M1.8 (PAL/I)
unnamed: U14.6 (B1), U14.9 (~Y3~)
unnamed: U14.3 (B0), U14.12 (~Y2~)
unnamed: U6.11 (D3), U16.2 (Z0), U19.35 (D11)
unnamed: U6.12 (D2), U16.3 (Z1), U19.36 (D10)
unnamed: U6.13 (D1), U16.9 (Z2), U19.37 (D9)
unnamed: U6.14 (D0), U16.10 (Z3), U19.38 (D8)
unnamed: U6.8 (~CS~), U27.11
PHI0: FB23.2; also elsewhere on the board
PHI2: CN6.E, U18.6 (PHI2); also elsewhere on the board
PHI_COLOR: U19.21 (PHI_COLOR); also elsewhere on the board
POTX: C48.1, U18.24 (POTX); also elsewhere on the board
POTY: C93.1, U18.23 (POTY); also elsewhere on the board
RDY: U27.8; also elsewhere on the board
R\~W~: CN6.5, R51.1, U9.3 (~WE~), U10.3 (~WE~), U11.3 (~WE~), U12.3 (~WE~), U17.24 (I11), U18.7 (R/~W~), U19.11 (R/~W~), U21.3 (~WE~), U22.3 (~WE~), U23.3 (~WE~), U24.3 (~WE~); also elsewhere on the board
~CHAREN~: U17.6 (I3); also elsewhere on the board
~CIA1~: U15.12 (2Y0); also elsewhere on the board
~CIA2~: U15.11 (2Y1); also elsewhere on the board
~HIRAM~: U17.7 (I2); also elsewhere on the board
~IRQ~: CN6.4, RP4.3, U19.8 (~IRQ~); also elsewhere on the board
~LORAM~: U17.8 (I1); also elsewhere on the board
~NMI~: CN6.D; also elsewhere on the board
~RESET~: FB4.2, U18.5 (~RES~); also elsewhere on the board
~VA14~: U14.2 (A0), U17.5 (I4); also elsewhere on the board
~VA15~: U14.5 (A1); also elsewhere on the board

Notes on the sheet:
RP1
RP2
BASIC
ROM
(A000-
BFFF)
KERNAL
(E000-
CHARACTER
(D000-
DFFF)
RP4 3.3K
Cartridge/Expansion (44 PIN FEMALE)
Multiplexed address bus
25V
-30L
COLOR RAM
AUDIO/VIDEO (8 PIN FEMALE DIN)
Y5U
SEE NOTE 5

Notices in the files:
250407_.kicad_pcb:
Licensed under CERN OHL v.1.2
